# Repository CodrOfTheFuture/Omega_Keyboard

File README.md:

# Omega

### Description:

Omega is an open source corne wireless keyboard that is built with the nice!nano v2. It includes an oled screen for each side and a low profile look. It looks great and great for coders, writers and any person who uses there keyboards a lot. In addition, Omega is built with the firmware called ZMK to allow bluetooth pairing.

### Why did I even make this:

A big reason why I started making this is because a problem I had with modern keyboards. They are not ergonomic and can be very damaging to someones wrists if they are typing for a long time. And since I am a coder who uses their keyboard a lot (i use vim), I face this problem.

Full 3d model of Omega

PCB:

Schematics:

|Name                  |Qty |Final Price- USD                |Link                                                    |
|----------------------|----|--------------------------------|--------------------------------------------------------|
|ProMicro              | 2  | 5.72                           | https://www.aliexpress.us/item/1005001621678794.html   |
|Lithium Battery 110mAh| 2  | 5.77                           | https://www.aliexpress.com/item/1005005348368664.html  |
|Machine Sockets       | 1  | 2.83                           | https://www.aliexpress.com/item/4001122376295.html     |
|Machine Pins          | 1  | 3.99                           | https://www.aliexpress.com/item/32858430771.html       |
|PCB                   | 2  | ~15.00 (including $20 discount & shipping) | https://jlcpcb.com/                        |
|3d printed case       | 2  | 10.00                          | printing locally                                       |
|OLED                  | 2  | 6.94                           | https://www.aliexpress.us/item/1005005301005280.html   |
|Choc Switches         | 50 | 25.00                          | https://www.aliexpress.com/item/1005008883418065.html  |
|choc keycaps          | 42 | 5.00                           | gonna print them locally                               |
|SMD diodes            | 100| 2.08                           | https://www.aliexpress.com/item/1005004629414782.html  |
|Kalih Hotswaps        | 50 | 6.85                           | https://www.aliexpress.com/item/1005008543325730.html  |
|Power Switch          | 5  | 0.69                           | https://lcsc.com/product-detail/image/SSSS811101_C109335.html |
|Reset Button          | 5  | 0.17                           | https://lcsc.com/product-detail/Tactile-Switches_G-Switch-GT-TC041B-H036-L1N_C2686893.html          |
|Battery Jack          | 5  | 0.71                           | https://lcsc.com/product-detail/image/S2B-PH-K-S-LF-SN_C173752.html          |
|Screw Kit             | 1  | 3.26                           | https://www.aliexpress.com/item/1005008459241647.html  |
|Soldering Iron        | 1  | 13.98                           | https://www.amazon.com/Soldering-Adjustable-Temperature-Electronics-Desoldering/dp/B097XX76V4/  |
|Shipement & other fees|    | 37.18                          | n/a                                                    |
|Total                 |    | 145.97                         |                                                        |

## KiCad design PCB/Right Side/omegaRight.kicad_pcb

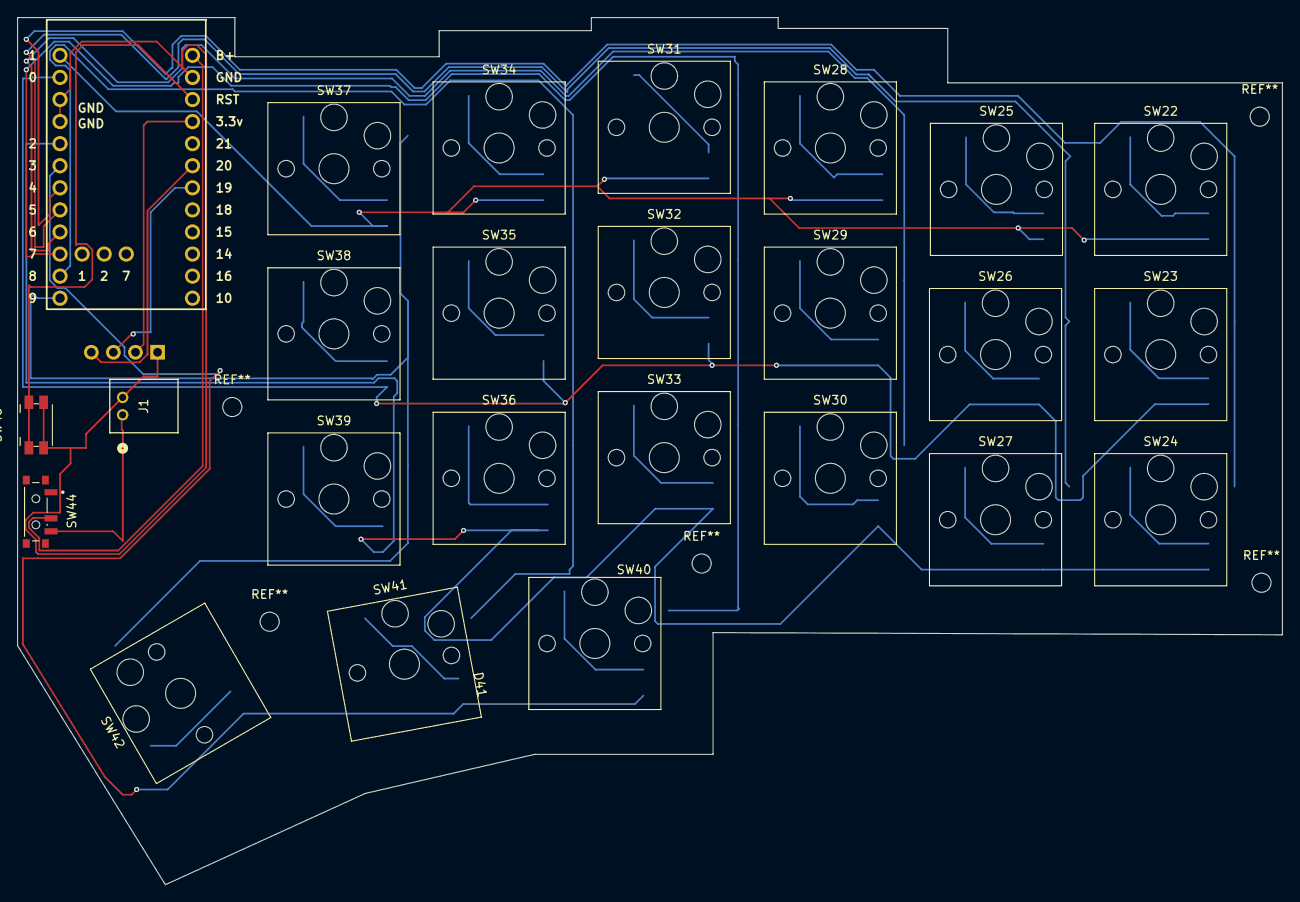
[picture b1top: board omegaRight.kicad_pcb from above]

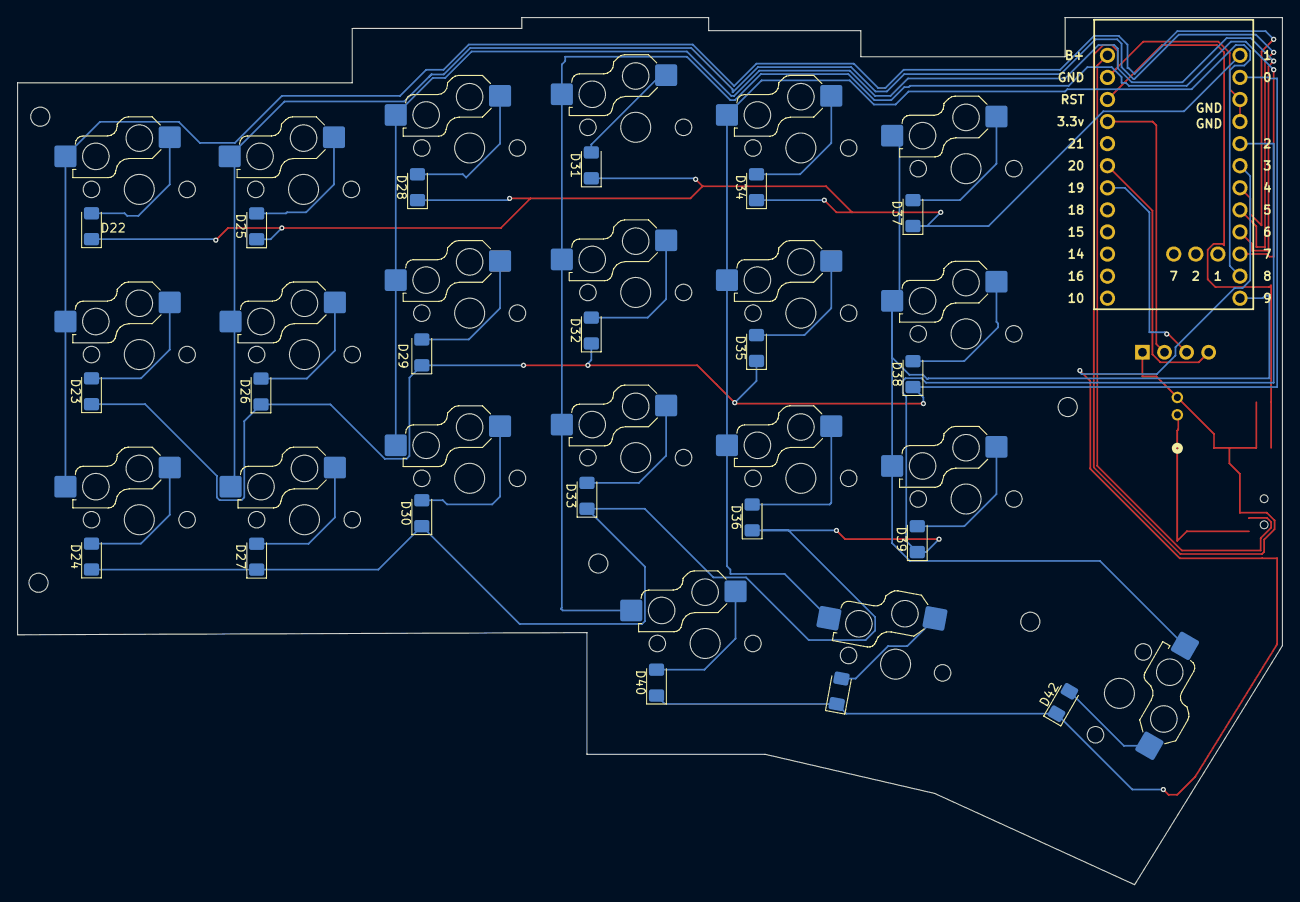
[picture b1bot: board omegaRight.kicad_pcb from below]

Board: 2 copper layers, 145.5 x 99.8 mm, 47 parts (21 on the bottom side), 38 nets.

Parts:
D22, D23, D24, D25, D26, D27, D28, D29, D30, D31, D32, D33, D34, D35, D36, D37, D38, D39, D40, D41, D42: D; D_1206_3216Metric_Pad1.42x1.75mm_HandSolder
J1: S2B-PH-K-SLFSN; CONN_S2B-PH-K-S_JST
J4: OLED_128x32
SW22, SW23, SW24, SW25, SW26, SW27, SW28, SW29, SW30, SW31, SW32, SW33, SW34, SW35, SW36, SW37, SW38, SW39, SW40, SW41, SW42: SW_Push; Hotswap_Choc_V1_1.00u
SW44: SW_SPDT; SW_SSSS811101
SW46: SW_Push; Panasonic_EVQPUJ_EVQPUA
U2: Nice_Nano_V2

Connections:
unnamed: D22.2 (A), SW22.1
unnamed: D23.2 (A), SW23.1
unnamed: D24.2 (A), SW24.1
unnamed: D25.2 (A), SW25.1
unnamed: D26.2 (A), SW26.1
unnamed: D27.2 (A), SW27.1
unnamed: D28.2 (A), SW28.1
unnamed: D29.2 (A), SW29.1
unnamed: D30.2 (A), SW30.1
unnamed: D31.2 (A), SW31.1
unnamed: D32.2 (A), SW32.1
unnamed: D33.2 (A), SW33.1
unnamed: D34.2 (A), SW34.1
unnamed: D35.2 (A), SW35.1
unnamed: D36.2 (A), SW36.1
unnamed: D37.2 (A), SW37.1
unnamed: D38.2 (A), SW38.1
unnamed: D39.2 (A), SW39.1
unnamed: D40.2 (A), SW40.1
unnamed: D41.2 (A), SW41.1
unnamed: D42.2 (A), SW42.1
unnamed: SW44.2 (B), U2.24 (B+)
unnamed: SW46.1, U2.22 (RST)
R_BATTERY_POSITIVE: J1.1, SW44.3 (C)
R_Col0: SW22.2, SW23.2, SW24.2, U2.7 (4)
R_Col1: SW25.2, SW26.2, SW27.2, U2.8 (5)
R_Col3: SW31.2, SW32.2, SW33.2, SW40.2, U2.10 (7)
R_Col4: SW34.2, SW35.2, SW36.2, SW41.2, U2.11 (8)
R_Col5: SW37.2, SW38.2, SW39.2, SW42.2, U2.12 (9)
R_Col 2: SW28.2, SW29.2, SW30.2, U2.9 (6)
R_GND: J1.2, J4.1 (GND), SW46.2, U2.3 (GND), U2.4 (GND), U2.23 (GND)
R_POWER_3.3V: J4.2 (VCC), U2.21 (3.3v)
R_Row0: D22.1 (K), D25.1 (K), D28.1 (K), D31.1 (K), D34.1 (K), D37.1 (K), U2.1
R_Row1: D23.1 (K), D26.1 (K), D29.1 (K), D32.1 (K), D35.1 (K), D38.1 (K), U2.2 (0)
R_Row2: D24.1 (K), D27.1 (K), D30.1 (K), D33.1 (K), D36.1 (K), D39.1 (K), U2.5 (2)
R_Row3: D40.1 (K), D41.1 (K), D42.1 (K), U2.6 (3)
R_SCL: J4.3 (SCL), U2.18 (19)
R_SDA: J4.4 (SDA), U2.19 (20)

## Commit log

2025-07-05 Day 3
2025-07-05 fixed picture not rendering
2025-07-08 Day 4-6
2025-07-09 day 7
2025-07-09 commiting Omega
2025-07-09 fixing budget
2025-07-25 changed BOM and readme
2025-07-25 updated BOM and README again
2025-07-31 organizing
2025-08-03 fixed image rendering
